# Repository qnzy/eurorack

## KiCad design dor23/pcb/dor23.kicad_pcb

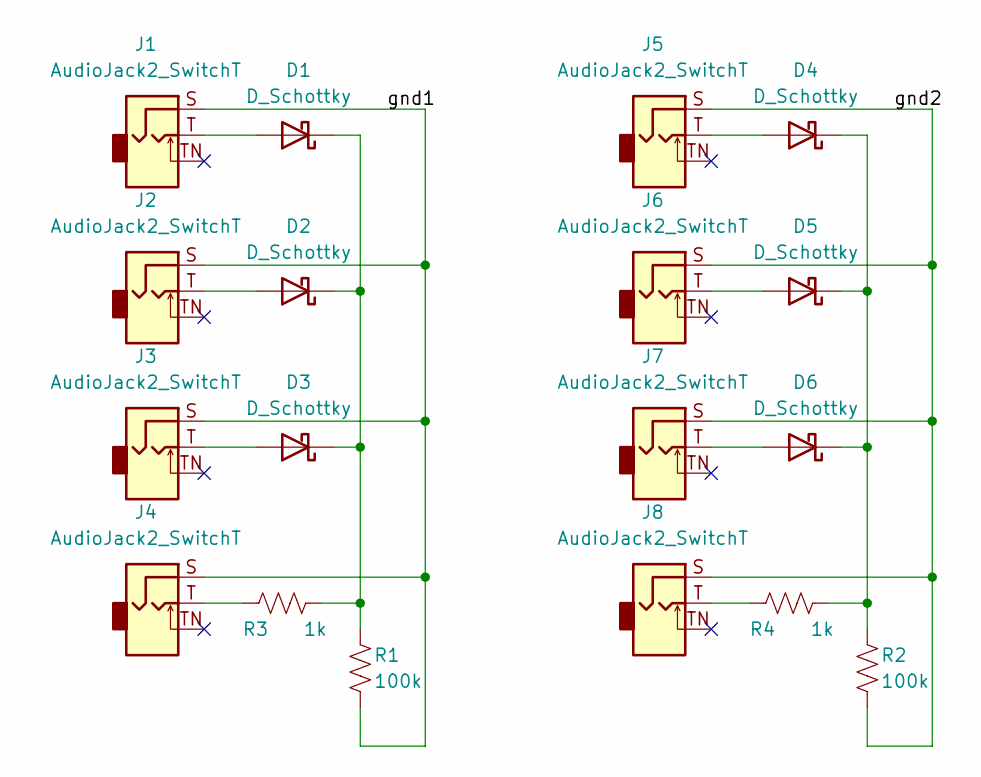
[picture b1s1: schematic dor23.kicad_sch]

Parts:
D1, D2, D3, D4, D5, D6: D_Schottky; D_SOD-123
J1, J2, J3, J4, J5, J6, J7, J8: AudioJack2_SwitchT; audio_jack_pj-398sm
R1, R2: 100k; R_0805_2012Metric_Pad1.20x1.40mm_HandSolder
R3, R4: 1k; R_0805_2012Metric_Pad1.20x1.40mm_HandSolder

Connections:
/gnd1: J1.S, J2.S, J3.S, J4.S, R1.2
/gnd2: J5.S, J6.S, J7.S, J8.S, R2.2
unnamed: D1.1 (K), D2.1 (K), D3.1 (K), R1.1, R3.2
unnamed: D1.2 (A), J1.T
unnamed: D2.2 (A), J2.T
unnamed: D3.2 (A), J3.T
unnamed: D4.1 (K), D5.1 (K), D6.1 (K), R2.1, R4.2
unnamed: D4.2 (A), J5.T
unnamed: D5.2 (A), J6.T
unnamed: D6.2 (A), J7.T
unnamed: J4.T, R3.1
unnamed: J8.T, R4.1

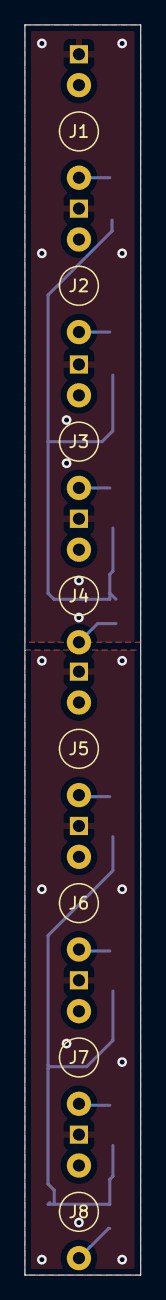
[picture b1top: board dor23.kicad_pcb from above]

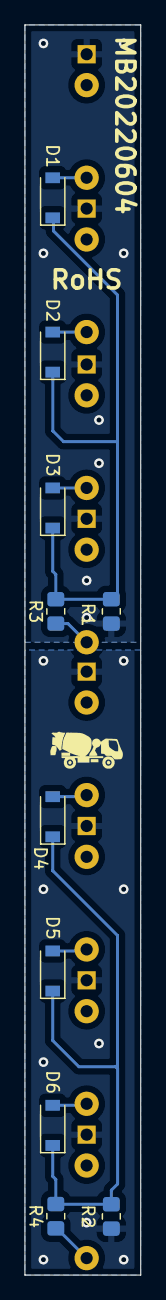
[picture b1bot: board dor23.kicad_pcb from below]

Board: 2 copper layers, 9.5 x 102.9 mm, 18 parts (10 on the bottom side), 12 nets.

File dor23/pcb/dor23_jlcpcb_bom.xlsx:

Comment | Designator | Footprint | JLCPCB Part #
Schottky Diode B5819W SL | D1, D2, D3, D4, D5, D6 | SOD-123 | C8598
100k | R1, R2 | R0805 | C25271
1k | R3, R4 | R0805 | C17513

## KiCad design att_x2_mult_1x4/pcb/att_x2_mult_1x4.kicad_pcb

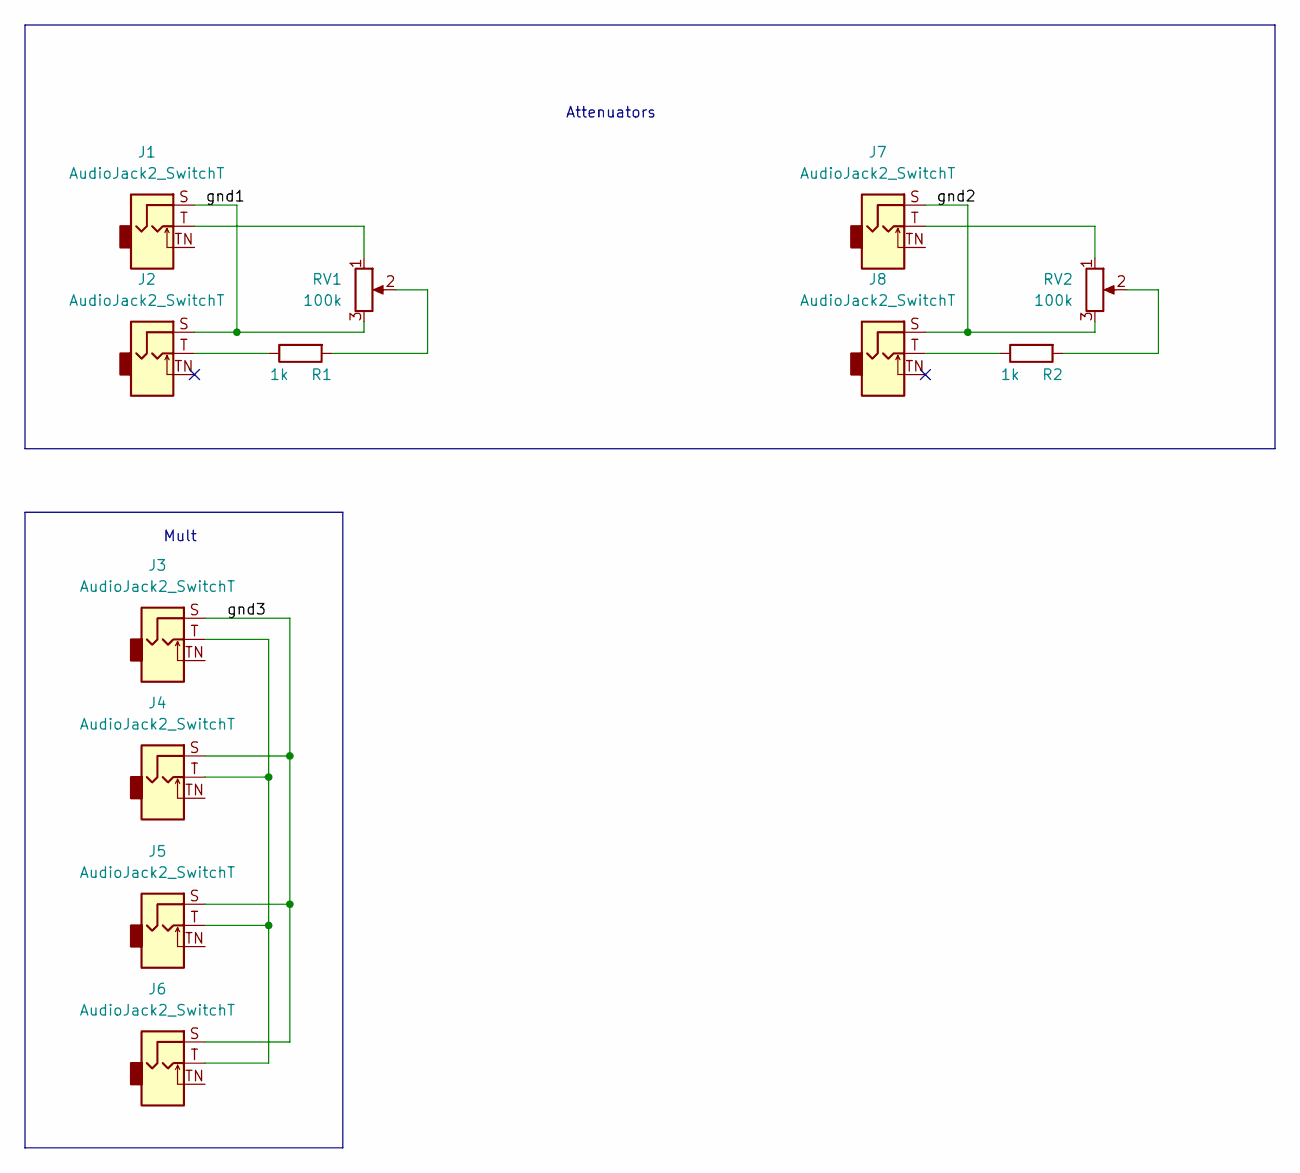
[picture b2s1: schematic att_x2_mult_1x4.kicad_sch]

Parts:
J1, J2, J3, J4, J5, J6, J7, J8: AudioJack2_SwitchT; audio_jack_pj-398sm
R1, R2: 1k; R_Axial_DIN0207_L6.3mm_D2.5mm_P10.16mm_Horizontal
RV1, RV2: 100k; pot1_B

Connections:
/gnd1: J1.S, J2.S, RV1.3
/gnd2: J7.S, J8.S, RV2.3
/gnd3: J3.S, J4.S, J5.S, J6.S
unnamed: J1.T, RV1.1
unnamed: J2.T, R1.1
unnamed: J3.T, J4.T, J5.T, J6.T
unnamed: J7.T, RV2.1
unnamed: J8.T, R2.1
unnamed: R1.2, RV1.2
unnamed: R2.2, RV2.2

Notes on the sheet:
Attenuators
Mult

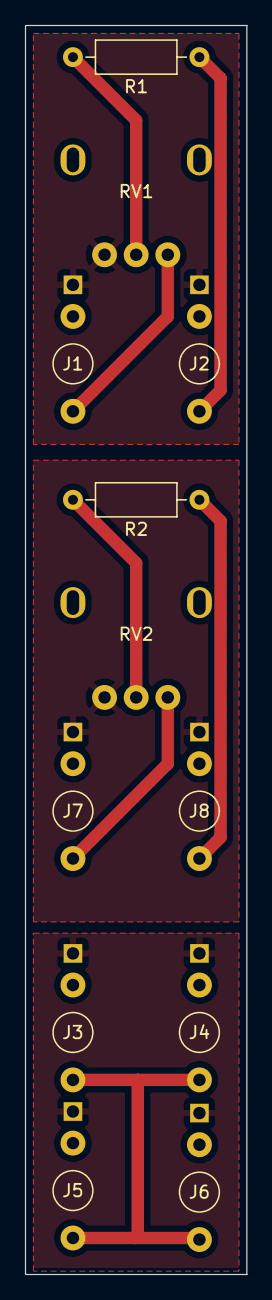
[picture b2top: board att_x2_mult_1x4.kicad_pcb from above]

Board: 2 copper layers, 17.8 x 100.3 mm, 12 parts (0 on the bottom side), 10 nets.

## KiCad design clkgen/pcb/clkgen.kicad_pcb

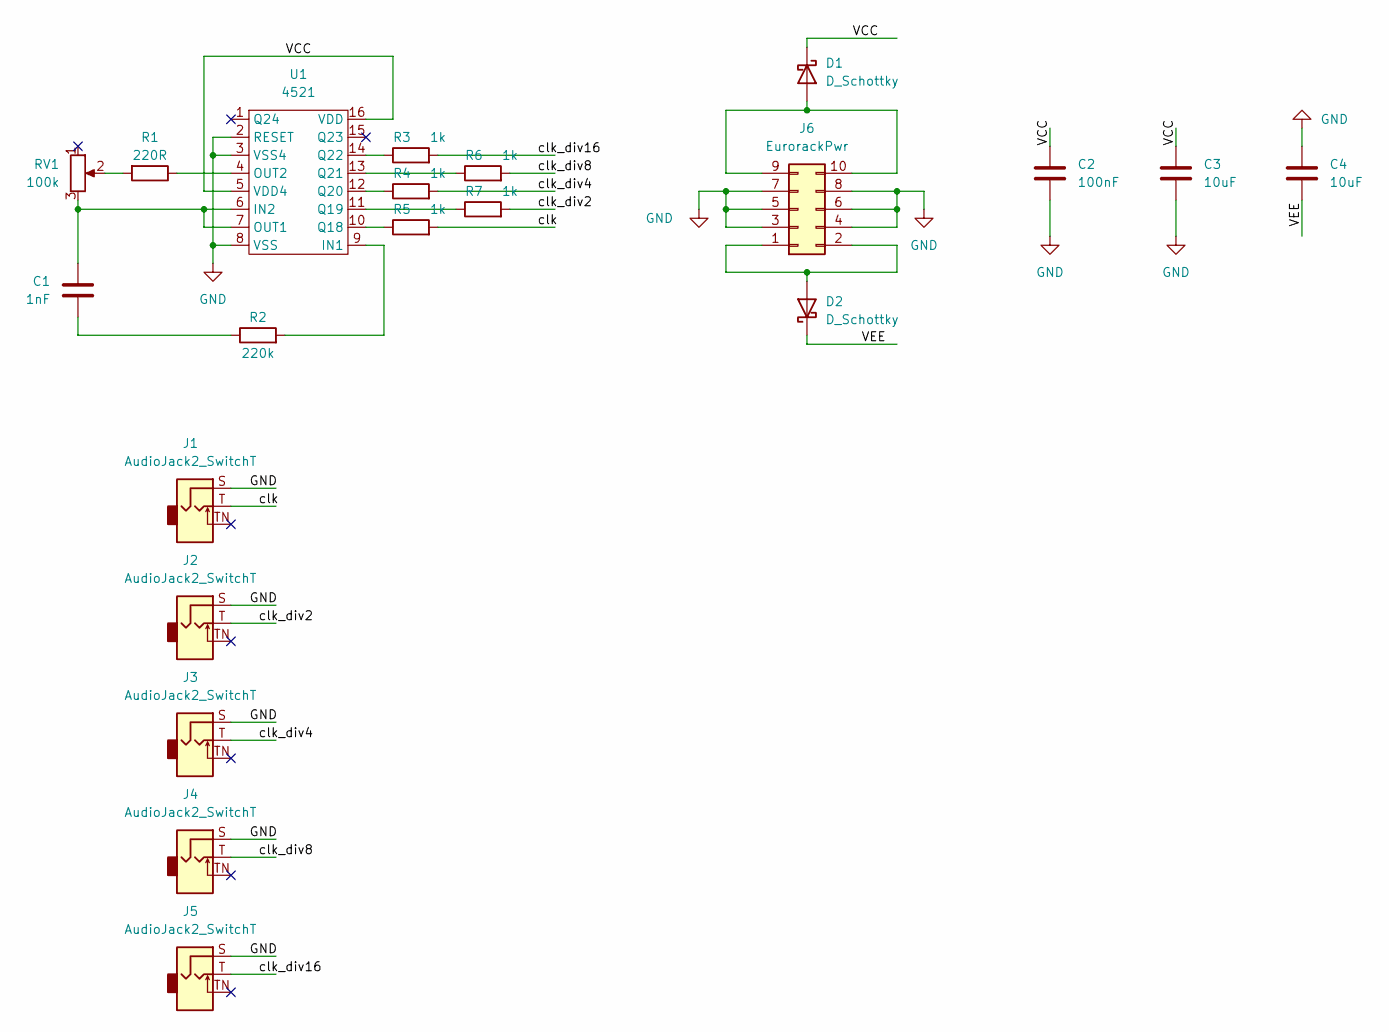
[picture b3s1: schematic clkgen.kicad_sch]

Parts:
C1: 1nF; C_0603_1608Metric
C2: 100nF; C_0603_1608Metric
C3, C4: 10uF; C_0603_1608Metric
D1, D2: D_Schottky; D_SOD-123
J1, J2, J3, J4, J5: AudioJack2_SwitchT; audio_jack_pj-398sm
J6: EurorackPwr; PinHeader_2x05_P2.54mm_Vertical
R1: 220R; R_0603_1608Metric
R2: 220k; R_0603_1608Metric
R3, R4, R5, R6, R7: 1k; R_0603_1608Metric
RV1: 100k; pot1_B
U1: 4521; SOIC-16_3.9x9.9mm_P1.27mm

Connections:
/VCC: C2.1, C3.1, D1.1 (K), U1.5 (VDD4), U1.16 (VDD)
/VEE: C4.2, D2.1 (K)
/clk: J1.T, R5.2
/clk_div2: J2.T, R7.2
/clk_div4: J3.T, R4.2
/clk_div8: J4.T, R6.2
/clk_div16: J5.T, R3.2
GND: C2.2, C3.2, C4.1, J1.S, J2.S, J3.S, J4.S, J5.S, J6.3, J6.4, J6.5, J6.6, J6.7, J6.8, U1.2 (RESET), U1.3 (VSS4), U1.8 (VSS)
unnamed: C1.1, R2.1
unnamed: C1.2, RV1.3, U1.6 (IN2), U1.7 (OUT1)
unnamed: D1.2 (A), J6.9, J6.10
unnamed: D2.2 (A), J6.1, J6.2
unnamed: R1.1, U1.4 (OUT2)
unnamed: R1.2, RV1.2
unnamed: R2.2, U1.9 (IN1)
unnamed: R3.1, U1.14 (Q22)
unnamed: R4.1, U1.12 (Q20)
unnamed: R5.1, U1.10 (Q18)
unnamed: R6.1, U1.13 (Q21)
unnamed: R7.1, U1.11 (Q19)

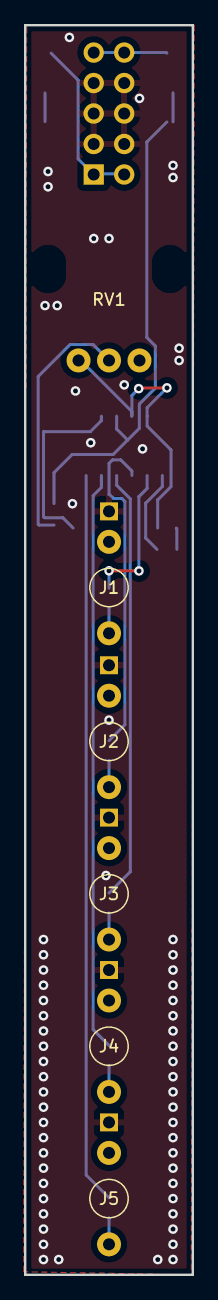
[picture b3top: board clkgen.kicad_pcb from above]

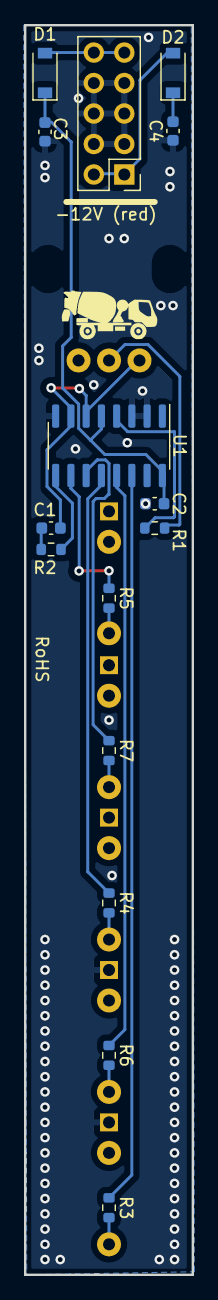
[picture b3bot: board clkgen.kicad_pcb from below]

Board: 2 copper layers, 14.0 x 104.1 mm, 21 parts (15 on the bottom side), 20 nets.

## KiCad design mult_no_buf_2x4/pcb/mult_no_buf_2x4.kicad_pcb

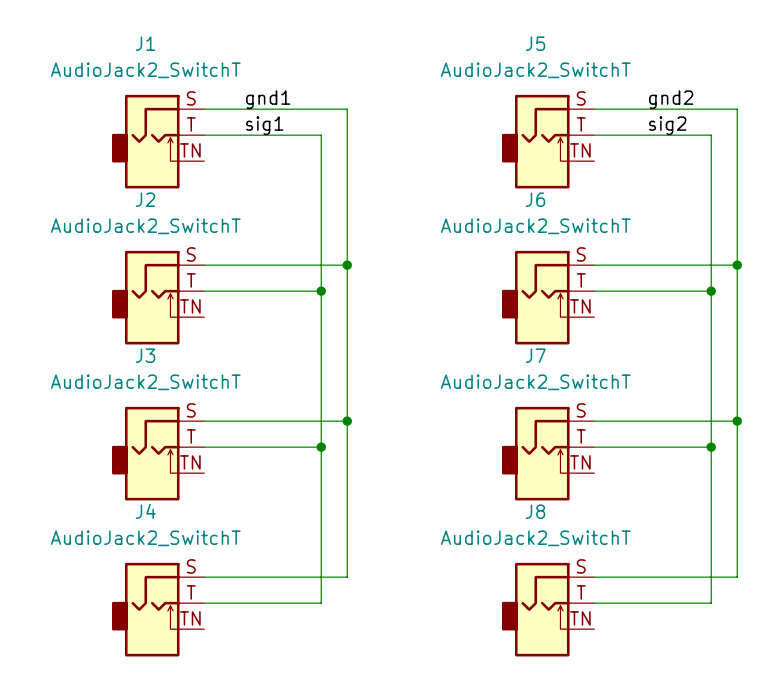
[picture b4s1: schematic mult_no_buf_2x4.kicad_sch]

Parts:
J1, J2, J3, J4, J5, J6, J7, J8: AudioJack2_SwitchT; audio_jack_pj-398sm

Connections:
/gnd1: J1.S, J2.S, J3.S, J4.S
/gnd2: J5.S, J6.S, J7.S, J8.S
/sig1: J1.T, J2.T, J3.T, J4.T
/sig2: J5.T, J6.T, J7.T, J8.T

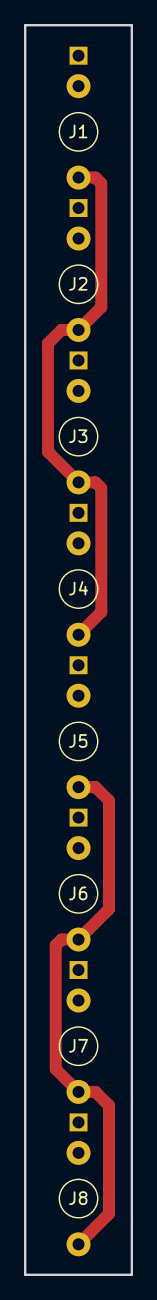
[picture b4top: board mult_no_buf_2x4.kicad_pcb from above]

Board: 2 copper layers, 8.9 x 104.1 mm, 8 parts (0 on the bottom side), 4 nets.

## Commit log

2022-06-04 added clkgen pcb
2022-06-05 updated drawing
2022-06-05 added bom
2022-06-06 first pcb layout
2022-06-06 rotated power connector ; added markings
2022-06-12 moved resistor, added scale to panel
2022-06-12 updated layout
2022-06-13 modified ring
2022-06-14 extended mult to 2x3
2022-06-14 added graphics folder
2022-06-16 revert cheanges on pat
2022-06-16 moved second attenuator slightly down
2022-06-17 replaced tht resistor with an smd
2022-06-22 updated pot footprint, changed rout back to tht
2022-07-04 Rename Musikbeton Ohne Text 01 Zeichenfläche 1.svg to musikbeton.svg
2022-07-04 Rename Musikbeton 01 Zeichenfläche 1.svg to musikbeton_mit_text.svg
2022-07-08 reverted panel ; change pot direction
2022-07-15 cosmetic changes (?)
2022-07-28 moved text
2022-07-29 initial commit of file
